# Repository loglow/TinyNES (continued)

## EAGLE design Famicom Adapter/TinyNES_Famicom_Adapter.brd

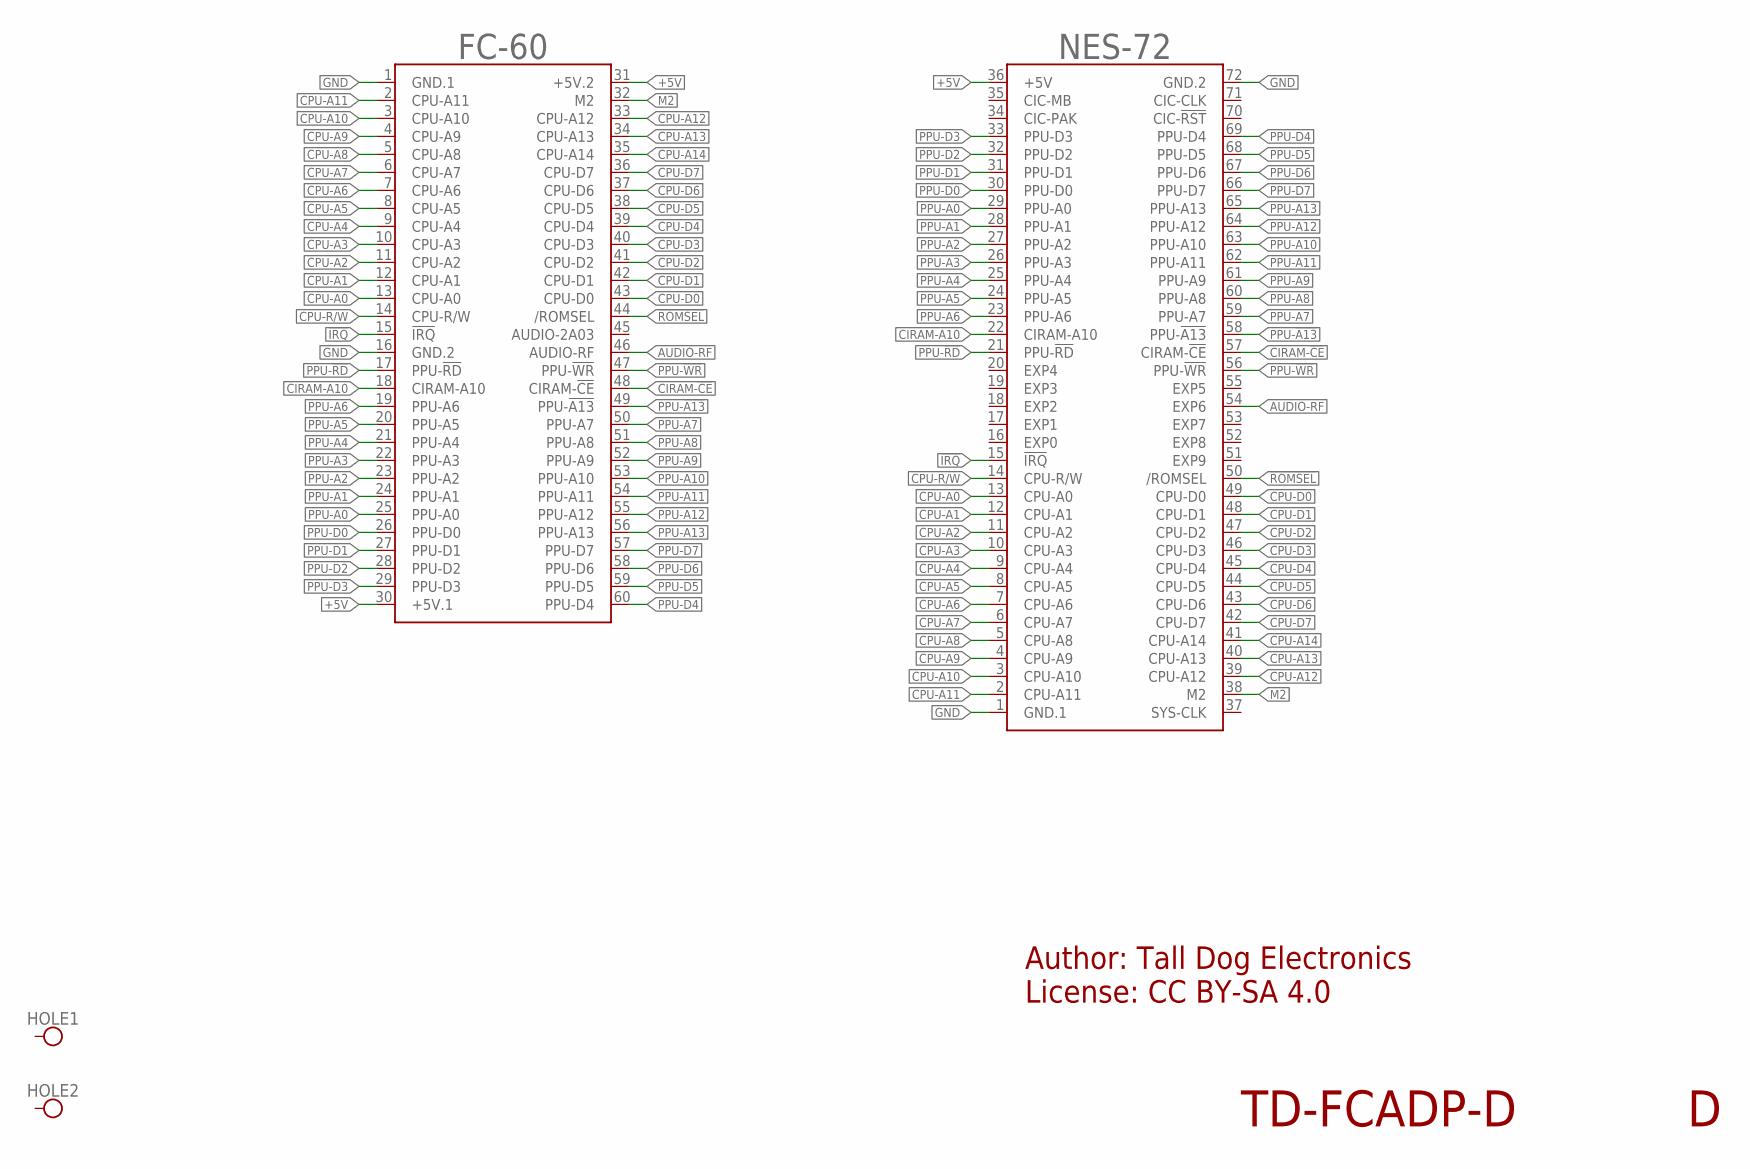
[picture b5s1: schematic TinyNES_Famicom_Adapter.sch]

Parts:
FC-60: CART-60-NAMES-CONN-EDGE; CART-60-2.54-CONN-EDGE
HOLE1, HOLE2: HOLE-M2.5
NES-72: CART-72-NAMES-GOLD-FINGERS; CART-72-2.50-GOLD-FINGERS

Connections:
!IRQ: FC-60.15 (!IRQ), NES-72.15 (!IRQ)
!ROMSEL: FC-60.44 (/ROMSEL), NES-72.50 (/ROMSEL)
+5V: FC-60.30 (+5V.1), FC-60.31 (+5V.2), NES-72.36 (+5V)
AUDIO-RF: FC-60.46 (AUDIO-RF), NES-72.54 (EXP6)
CIRAM-!CE: FC-60.48 (CIRAM-!CE), NES-72.57 (CIRAM-!CE)
CIRAM-A10: FC-60.18 (CIRAM-A10), NES-72.22 (CIRAM-A10)
CPU-A0: FC-60.13 (CPU-A0), NES-72.13 (CPU-A0)
CPU-A1: FC-60.12 (CPU-A1), NES-72.12 (CPU-A1)
CPU-A2: FC-60.11 (CPU-A2), NES-72.11 (CPU-A2)
CPU-A3: FC-60.10 (CPU-A3), NES-72.10 (CPU-A3)
CPU-A4: FC-60.9 (CPU-A4), NES-72.9 (CPU-A4)
CPU-A5: FC-60.8 (CPU-A5), NES-72.8 (CPU-A5)
CPU-A6: FC-60.7 (CPU-A6), NES-72.7 (CPU-A6)
CPU-A7: FC-60.6 (CPU-A7), NES-72.6 (CPU-A7)
CPU-A8: FC-60.5 (CPU-A8), NES-72.5 (CPU-A8)
CPU-A9: FC-60.4 (CPU-A9), NES-72.4 (CPU-A9)
CPU-A10: FC-60.3 (CPU-A10), NES-72.3 (CPU-A10)
CPU-A11: FC-60.2 (CPU-A11), NES-72.2 (CPU-A11)
CPU-A12: FC-60.33 (CPU-A12), NES-72.39 (CPU-A12)
CPU-A13: FC-60.34 (CPU-A13), NES-72.40 (CPU-A13)
CPU-A14: FC-60.35 (CPU-A14), NES-72.41 (CPU-A14)
CPU-D0: FC-60.43 (CPU-D0), NES-72.49 (CPU-D0)
CPU-D1: FC-60.42 (CPU-D1), NES-72.48 (CPU-D1)
CPU-D2: FC-60.41 (CPU-D2), NES-72.47 (CPU-D2)
CPU-D3: FC-60.40 (CPU-D3), NES-72.46 (CPU-D3)
CPU-D4: FC-60.39 (CPU-D4), NES-72.45 (CPU-D4)
CPU-D5: FC-60.38 (CPU-D5), NES-72.44 (CPU-D5)
CPU-D6: FC-60.37 (CPU-D6), NES-72.43 (CPU-D6)
CPU-D7: FC-60.36 (CPU-D7), NES-72.42 (CPU-D7)
CPU-R/W: FC-60.14 (CPU-R/W), NES-72.14 (CPU-R/W)
GND: FC-60.1 (GND.1), FC-60.16 (GND.2), NES-72.1 (GND.1), NES-72.72 (GND.2)
M2: FC-60.32 (M2), NES-72.38 (M2)
PPU-!A13: FC-60.49 (PPU-!A13), NES-72.58 (PPU-!A13)
PPU-!RD: FC-60.17 (PPU-!RD), NES-72.21 (PPU-!RD)
PPU-!WR: FC-60.47 (PPU-!WR), NES-72.56 (PPU-!WR)
PPU-A0: FC-60.25 (PPU-A0), NES-72.29 (PPU-A0)
PPU-A1: FC-60.24 (PPU-A1), NES-72.28 (PPU-A1)
PPU-A2: FC-60.23 (PPU-A2), NES-72.27 (PPU-A2)
PPU-A3: FC-60.22 (PPU-A3), NES-72.26 (PPU-A3)
PPU-A4: FC-60.21 (PPU-A4), NES-72.25 (PPU-A4)
PPU-A5: FC-60.20 (PPU-A5), NES-72.24 (PPU-A5)
PPU-A6: FC-60.19 (PPU-A6), NES-72.23 (PPU-A6)
PPU-A7: FC-60.50 (PPU-A7), NES-72.59 (PPU-A7)
PPU-A8: FC-60.51 (PPU-A8), NES-72.60 (PPU-A8)
PPU-A9: FC-60.52 (PPU-A9), NES-72.61 (PPU-A9)
PPU-A10: FC-60.53 (PPU-A10), NES-72.63 (PPU-A10)
PPU-A11: FC-60.54 (PPU-A11), NES-72.62 (PPU-A11)
PPU-A12: FC-60.55 (PPU-A12), NES-72.64 (PPU-A12)
PPU-A13: FC-60.56 (PPU-A13), NES-72.65 (PPU-A13)
PPU-D0: FC-60.26 (PPU-D0), NES-72.30 (PPU-D0)
PPU-D1: FC-60.27 (PPU-D1), NES-72.31 (PPU-D1)
PPU-D2: FC-60.28 (PPU-D2), NES-72.32 (PPU-D2)
PPU-D3: FC-60.29 (PPU-D3), NES-72.33 (PPU-D3)
PPU-D4: FC-60.60 (PPU-D4), NES-72.69 (PPU-D4)
PPU-D5: FC-60.59 (PPU-D5), NES-72.68 (PPU-D5)
PPU-D6: FC-60.58 (PPU-D6), NES-72.67 (PPU-D6)
PPU-D7: FC-60.57 (PPU-D7), NES-72.66 (PPU-D7)

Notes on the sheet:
TD-FCADP-D
Author: Tall Dog Electronics License: CC BY-SA 4.0

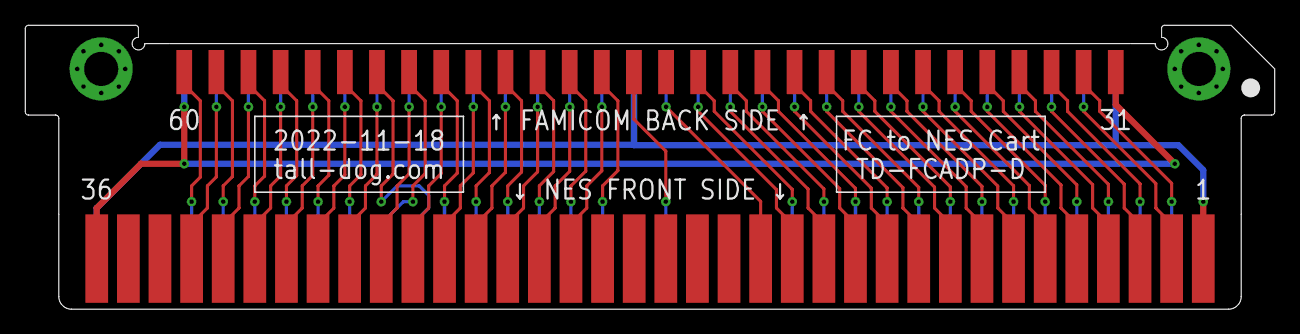
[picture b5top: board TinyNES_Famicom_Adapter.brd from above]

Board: 2 copper layers, 98.8 x 22.4 mm, 4 parts (1 on the bottom side), 57 nets.

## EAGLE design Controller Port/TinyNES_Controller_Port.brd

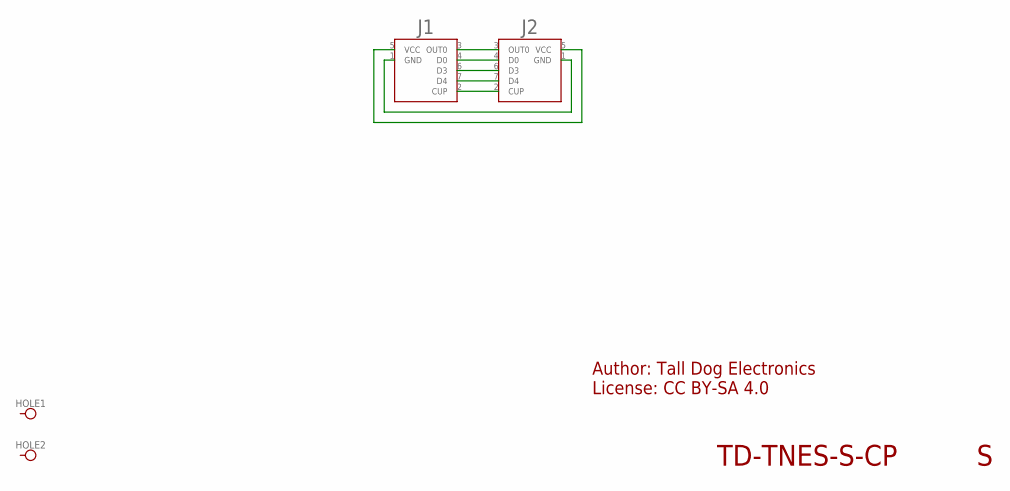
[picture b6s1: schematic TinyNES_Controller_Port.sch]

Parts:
HOLE1, HOLE2: HOLE-M2.5
J1: CTRL; JST-PH-7
J2: CTRL-NES; NES-CTRL

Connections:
CUP: J1.2 (CUP), J2.2 (CUP)
D0: J1.4 (D0), J2.4 (D0)
D3: J1.6 (D3), J2.6 (D3)
D4: J1.7 (D4), J2.7 (D4)
GND: J1.1 (GND), J2.1 (GND)
OUT0: J1.3 (OUT0), J2.3 (OUT0)
VCC: J1.5 (VCC), J2.5 (VCC)

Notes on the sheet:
TD-TNES-S-CP
Author: Tall Dog Electronics License: CC BY-SA 4.0

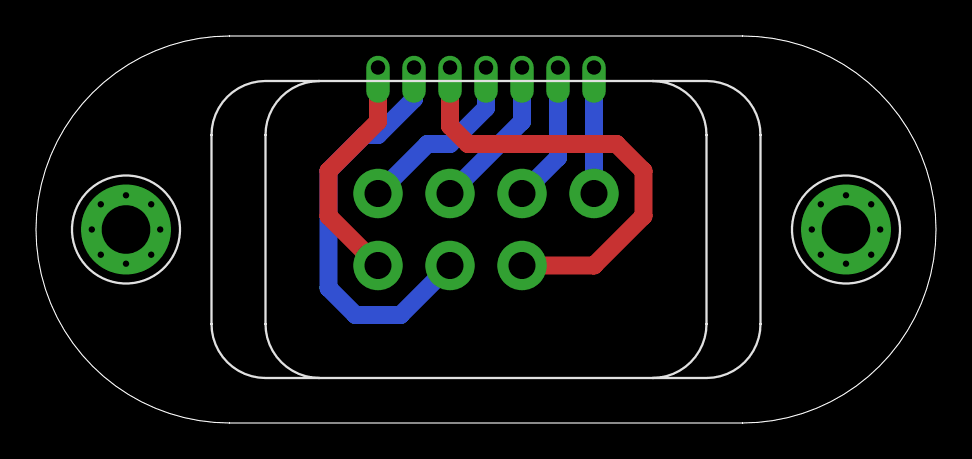
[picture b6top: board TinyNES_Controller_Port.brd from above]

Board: 2 copper layers, 50.0 x 21.5 mm, 4 parts (1 on the bottom side), 7 nets.

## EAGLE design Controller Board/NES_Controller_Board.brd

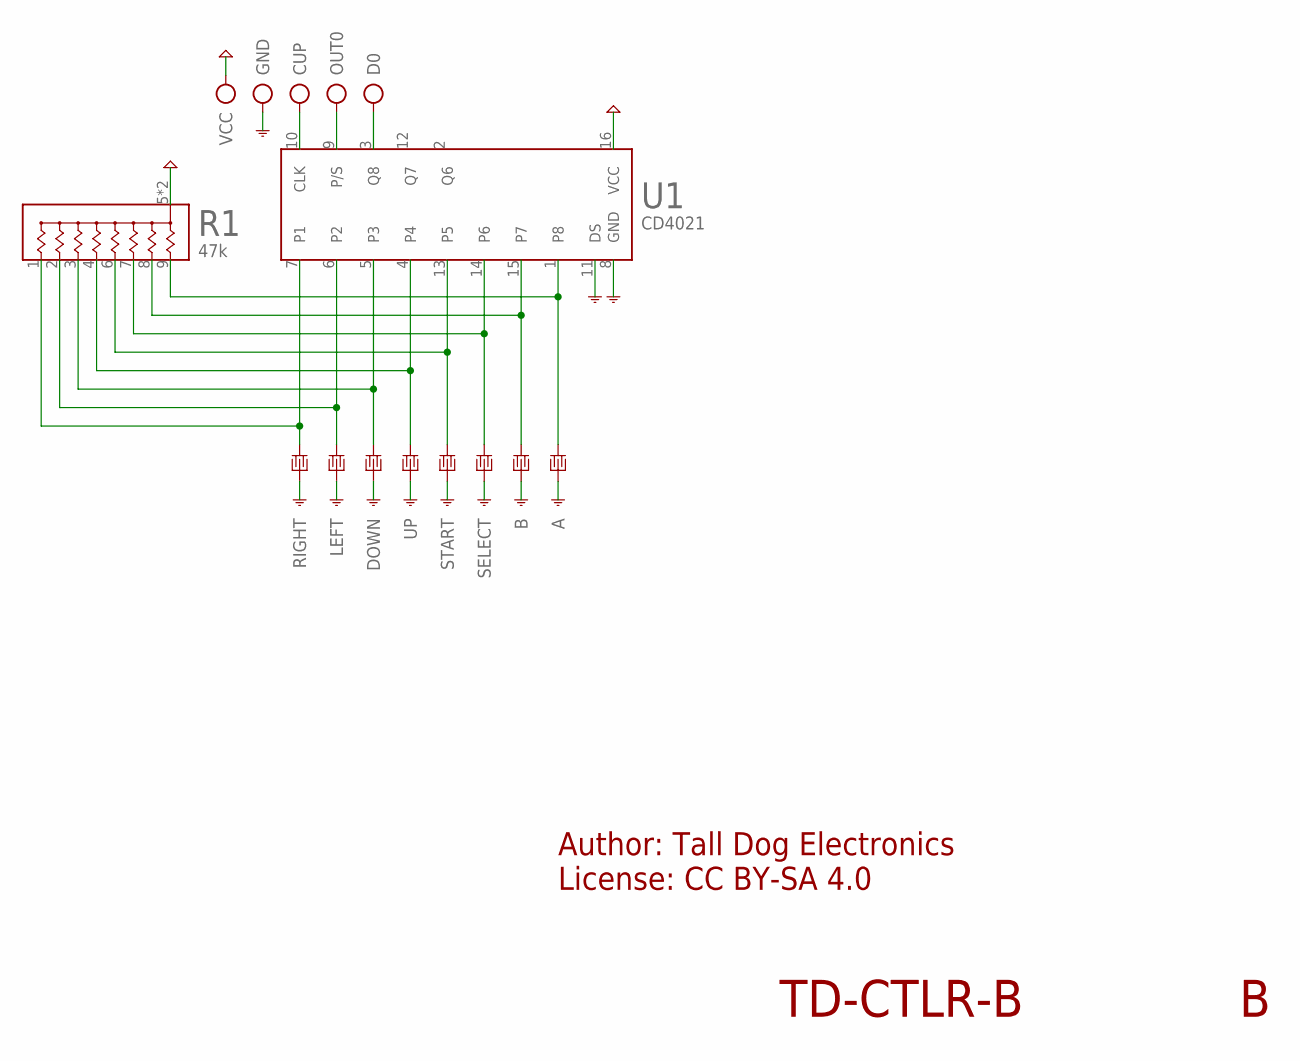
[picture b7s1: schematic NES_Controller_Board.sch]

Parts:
A: BUTTON-PAD-AB; CTRL-AB
B: BUTTON-PAD-AB; CTRL-AB
CUP: 2/RD; PTH-STRAIN
D0: 4/YL; PTH-STRAIN
DOWN: BUTTON-PAD-DPAD; CTRL-DPAD
GND: 1/BN; PTH-STRAIN
LEFT: BUTTON-PAD-DPAD; CTRL-DPAD
OUT0: 3/OR; PTH-STRAIN
R1: 47k; EXBA10P
RIGHT: BUTTON-PAD-DPAD; CTRL-DPAD
SELECT: BUTTON-PAD-STSEL; CTRL-STSEL
START: BUTTON-PAD-STSEL; CTRL-STSEL
U1: CD4021; SOIC-16
UP: BUTTON-PAD-DPAD; CTRL-DPAD
VCC: 5/WH; PTH-STRAIN

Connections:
CUP: CUP.A, CUP.P, U1.10 (CLK)
D0: D0.A, D0.P, U1.3 (Q8)
GND: A.A, B.A, DOWN.A, GND.A, GND.P, LEFT.A, RIGHT.A, SELECT.A, START.A, U1.8 (GND), U1.11 (DS), UP.A
unnamed: LEFT.B, R1.2, U1.6 (P2)
unnamed: R1.4, U1.4, UP.B
unnamed: DOWN.B, R1.3, U1.5 (P3)
unnamed: R1.1, RIGHT.B, U1.7 (P1)
unnamed: R1.6 (5), START.B, U1.13 (P5)
unnamed: R1.7 (6), SELECT.B, U1.14 (P6)
unnamed: B.B, R1.8 (7), U1.15 (P7)
unnamed: A.B, R1.9 (8), U1.1 (P8)
OUT0: OUT0.A, OUT0.P, U1.9 (P/S)
VCC: R1.5 (COM), R1.10 (COM), U1.16 (VCC), VCC.A, VCC.P

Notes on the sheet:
TD-CTLR-B
Author: Tall Dog Electronics License: CC BY-SA 4.0

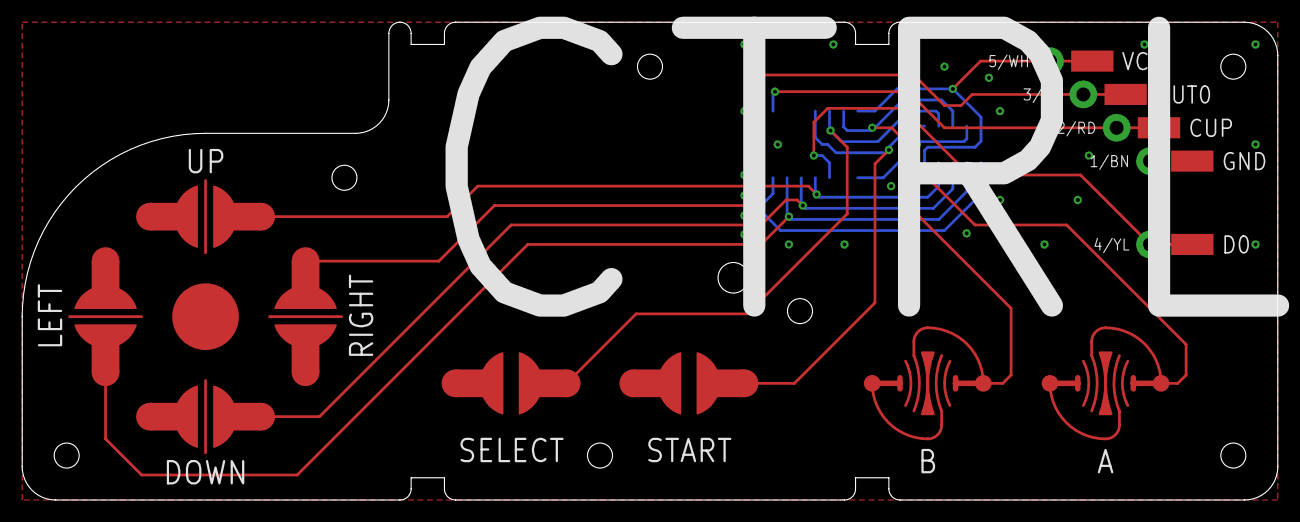
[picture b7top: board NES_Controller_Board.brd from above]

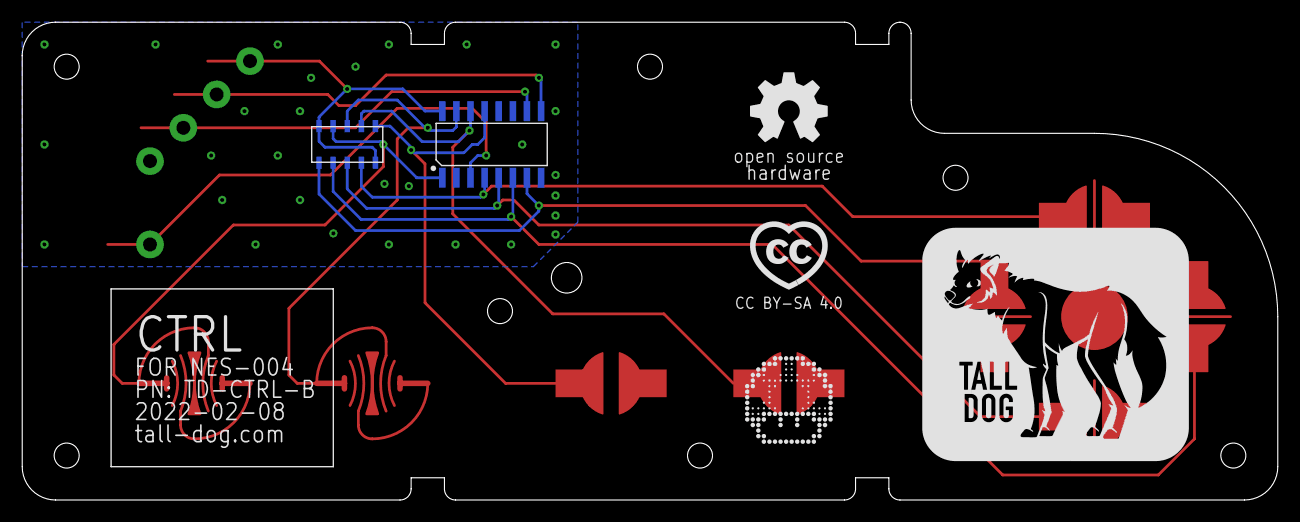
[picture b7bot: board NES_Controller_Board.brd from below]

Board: 2 copper layers, 113.0 x 43.0 mm, 19 parts (11 on the bottom side), 13 nets.

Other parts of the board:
U$1: _LOGO-TALL-DOG
U$2: _PIXEL-ART-1UP
U$3: _LOGO-OSH
U$4: _LOGO-CC-BY-SA

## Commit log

2022-03-21 first commit of all project files
2022-03-21 Create LICENSE
2022-03-24 Added OSHWA cert number
2022-07-28 Added accessory packaging labels
2022-07-28 Main board revisions for production version
2022-07-28 Prep for RGB board option
2022-10-26 Minor cleanup
2024-04-02 enclosure date and version update
2024-04-02 controller port date update
2024-04-02 famicom adapter date update
2024-04-02 added jumper board files
2024-04-02 updated labels with new version
2024-04-02 main board version updates
2024-04-02 packaging and manual revision updates
2024-04-02 plastic part revisions
2024-04-02 added .DS_Store to ignored files
2024-04-02 added RGB board files
2024-04-02 added RGBS to YPbPr adapter files
2024-04-02 updated base files for new revision
2024-07-05 Updates in preparation for next production run (Main Board Rev 27)
2024-07-05 Manual revision for very minor typo fix
2024-07-20 small part change update
2024-07-26 minor resistor component value change
